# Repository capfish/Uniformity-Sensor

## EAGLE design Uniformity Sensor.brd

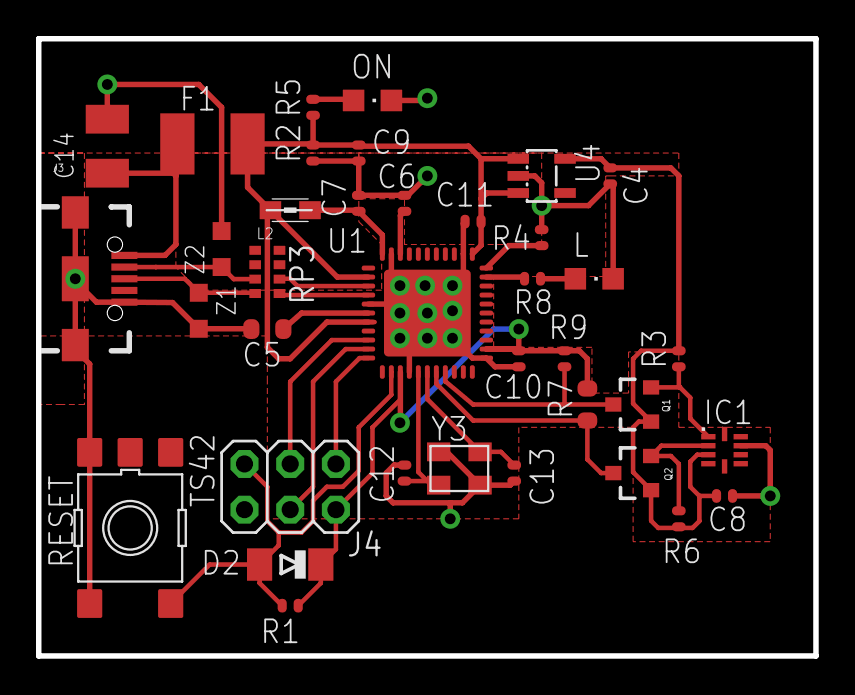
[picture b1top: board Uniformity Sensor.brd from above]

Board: 2 copper layers, 43.2 x 34.3 mm, 37 parts (0 on the bottom side), 25 nets.

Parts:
C4, C7, C8: 1uF; C0402
C5: 1uF; SMARTPRJ_C0603-ROUND
C6, C9, C10, C11: 100n; C0402
C12, C13: 22pF; C0402
C14: 22u; SMC_B
D2: CD1206-S01575; MINIMELF
F1: MF-MSMF050-2 500mA; L1812
IC1: SI1145; QFN-10
J3: USB-MICRO!!!; USB-B-MICRO-SMD_V03
J4: 3x2M; 2X03
L: green; CHIPLED_0805
L2: MH2029-300Y; 0805
ON: blue; CHIPLED_0805
Q1, Q2: 200mA/50V; SOT23-3
R1, R2, R4: 10K; R0402
R3, R6, R9: SMARTPRJ_R0402
R5, R8: 1K; R0402
R7: SMARTPRJ_R0603-ROUND
RESET: TS42
RP3: 22R; CAY16
U1: ATMEGA32U4-XUMU; QFN44ML7X7
U4: LP2985-33DBVR; SOT23-DBV
Y3: 16MHz KX-7; CRYSTAL-3.2-2.5
Z1, Z2: CG0603MLC-05E; CT/CN0603

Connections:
3V3: C4.1, C8.1, IC1.3, Q1.1, Q2.1, R3.2, R6.2, U4.5
AREF: C6.1, U1.42
AVCC: C7.1, L2.2, U1.44
D+: J3.D+, RP3.8, Z1.1
D-: J3.D-, RP3.7, Z2.1
GND: C4.2, C5.2, C6.2, C7.2, C8.2, C9.2, C10.2, C11.2, C12.1, C13.1, C14.-, IC1.8, J3.GND, J3.SHIELD1, J3.SHIELD2, J3.SHIELD3, J4.6, L.C, ON.C, R2.1, R4.2, RESET.3, RESET.4, U1.5, U1.15, U1.23, U1.35, U1.43, U1.EXP, U4.2, Y3.2, Y3.4, Z1.2, Z2.2
HWB: R4.1, U1.33
IO13*: R8.1, U1.32
MISO: J4.1, U1.11
MOSI: J4.4, U1.10
unnamed: IC1.1, Q1.2, R3.1
unnamed: ON.A, R5.2
unnamed: IC1.2, Q2.2, R6.1
unnamed: L.A, R8.2
RD+: RP3.1, U1.4
RD-: RP3.2, U1.3
RESET: D2.A, J4.5, R1.2, RESET.2, U1.13
SCK: J4.3, U1.9
SCL: Q2.3, R7.1, U1.18
SDA: Q1.3, R9.1, U1.19
UCAP: C5.1, U1.6
VUSB: C9.1, C10.1, C11.1, D2.C, F1.2, J4.2, L2.1, R1.1, R2.2, R5.1, R7.2, R9.2, U1.2, U1.7, U1.14, U1.24, U1.34, U4.1, U4.3
VUSBD: C14.+, F1.1, J3.VBUS
XTAL1: C13.2, U1.17, Y3.3
XTAL2: C12.2, U1.16, Y3.1

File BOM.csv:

Qty,Value,Device,Package,Parts,,Description,PROD_ID     VALUE3,,SMARTPRJ_R-EU_R0402,SMARTPRJ_R0402,"R3, R6,",R9,"RESISTOR, European symbol",1,,SMARTPRJ_R-EU_R0603,SMARTPRJ_R0603-ROUND,R7,,"RESISTOR, European symbol",4,100n,C-EUC0402,C0402,"C6, C9,","C10, C11","CAPACITOR, European symbol",3,10K,R-EU_R0402,R0402,"R1, R2,",R4,"RESISTOR, European symbol",1,16MHz KX-7,CRYSTAL-3.2-2.5,CRYSTAL-3.2-2.5,Y3,,,2,1K,R-EU_R0402,R0402,"R5, R8",,"RESISTOR, European symbol",3,1uF,C-EUC0402,C0402,"C4, C7,",C8,"CAPACITOR, European symbol",1,1uF,SMARTPRJ_C-EUC0603,SMARTPRJ_C0603-ROUND,C5,,"CAPACITOR, European symbol",2,200mA/50V,MOSFET-NCHANNELBSS138,SOT23-3,"Q1, Q2",,Common NMOSFET Parts,TRANS-00830 200mA/50V1,22R,4R-NCAY16,CAY16,RP3,,Array Chip Resistor,2,22pF,C-EUC0402,C0402,"C12, C1",3,"CAPACITOR, European symbol",1,22u,CPOL-EUSMCB,SMC_B,C14,,"POLARIZED CAPACITOR, European",symbol1,3x2M,PINHD-2X3,2X03,J4,,PIN HEADER,1,ATMEGA32U4-XUMU,ATMEGA32U4-XUMU,QFN44ML7X7,U1,,,1,CD1206-S01575,DIODE-MINIMELF,MINIMELF,D2,,DIODE,2,CG0603MLC-05E,VARISTORCN0603,CT/CN0603,"Z1, Z2",,VARISTOR,1,LP2985-33DBVR,LP2985-XXDBVR33,SOT23-DBV,U4,,ULTRALOW-POWER 50-mA LOW-DROP,OUT LINEAR REGULATORS1,MF-MSMF050-2 500mA,L-EUL1812,L1812,F1,,"INDUCTOR, European symbol",1,MH2029-300Y,WE-CBF_0805,805,L2,,SMD EMI Suppression Ferrite B,eads1,SI1145,SI1145,QFN-10,IC1,,PROXIMITY/UV/AMBIENT LIGHT SE,NSOR IC WITH I2C INTERFACE1,TS42,TS42,TS42,RESET,,TS42,1,USB-MICRO!!!,"USB-MICROB""",USB-B-MICRO-SMD_V03,J3,,,CONN-117521,blue,LEDCHIPLED_0805,CHIPLED_0805,ON,,LED,1,green,LEDCHIPLED_0805,CHIPLED_0805,L,,LED,

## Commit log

2016-03-16 most board placement
2016-03-16 some routing
2016-03-16 probably routed
2016-03-17 Gerber and BOM
2016-03-21 ordered version

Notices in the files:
parts and their libraries:
SparkFun-DiscreteSemi: Licensing: Creative Commons ShareAlike 4.0 International - https://creativecommons.org/licenses/by-sa/4.0
